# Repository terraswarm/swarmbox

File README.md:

SwarmBox
========

Testbed for the swarm of things.

Additional details documented in the [Terraswarm wiki](http://www.terraswarm.org/testbeds/wiki/Main/Hardware, "Terraswarm wiki, Hardware")

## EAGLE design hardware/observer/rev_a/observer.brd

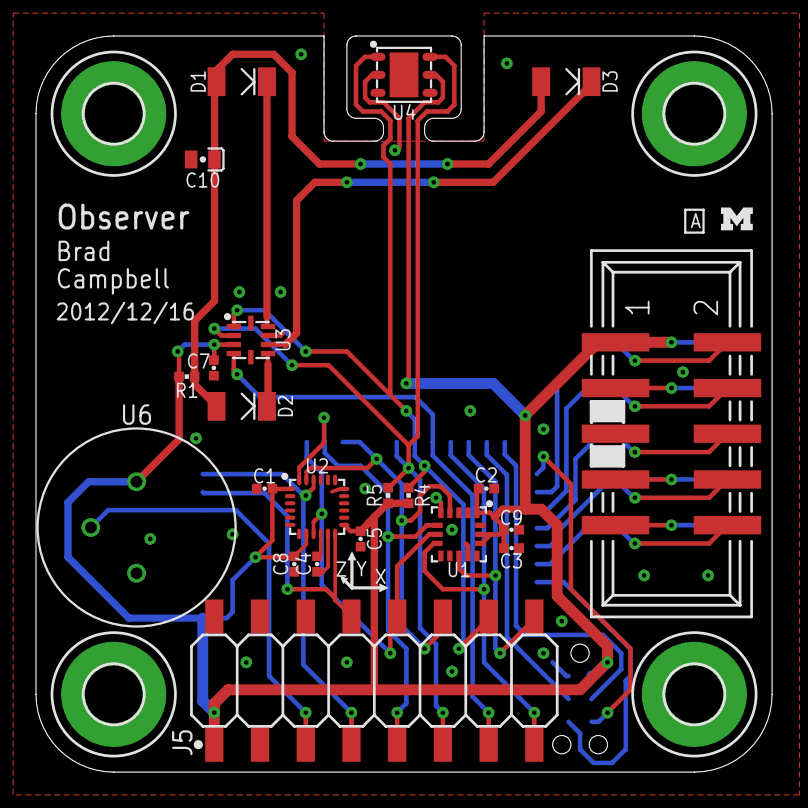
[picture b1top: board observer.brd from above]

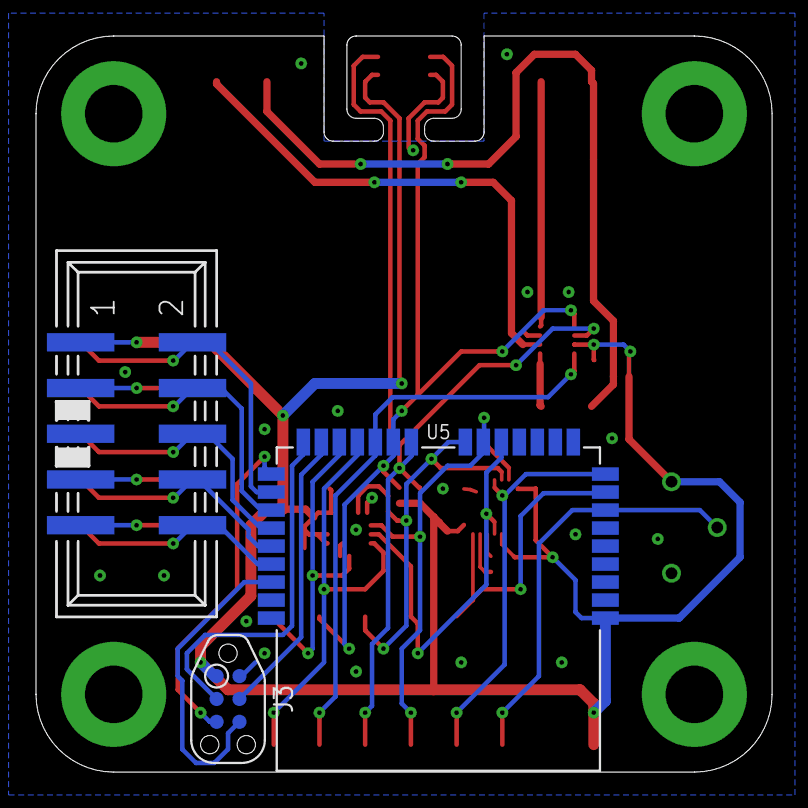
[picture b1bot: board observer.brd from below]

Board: 2 copper layers, 40.9 x 40.9 mm, 30 parts (3 on the bottom side), 29 nets.

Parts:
C1: 10nF; 0402_CAP
C2, C3, C4, C5, C7, C8: 0.1uF; 0402_CAP
C9: 10uF; 0402_CAP
C10: 22uF; CAP0603
D1, D2, D3: SFH4056
H5, H6, H7, H8: MOUNT-PAD-ROUND3.2; 3,2-PAD
J1, J2: CON_HEADER_2X05-SMD+SHROUDED; PINSHRD_SMT_2X05
J3: TC2030-CC2538-BL-NL; TC2030-IDC-NL
J5: PINHD-2X8/SMD; 2X8/SMD
LOGO1: UMICH_SOLID_TINY; UMICH_SOLID_50MIL
R1: 30; 0402_RES
R4, R5: 10k; 0402_RES
U1: LPS331AP; HCLGA-16/3MM
U2: MPU-9250; QFN-24/3MM
U3: SI1147; QFN-10/2MM
U4: SI7021; DFN-6/3MM
U5: ATUM
U6: AMN41121; AMN2

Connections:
5V: J1.3, J2.3
!ACCEL_CS: J5.7, U2.22, U5.9
!BBB_CS: J1.8, J2.8, U5.28
!PRESSURE_CS: J5.15, U1.8, U5.20
!RESET: J3.6, U5.30
ACCEL_INT: J5.8, U2.12, U5.8
BBB_GPIO: J1.7, J2.7
BBB_INT: J1.10, J2.10, U5.29
BBB_MISO: J1.4, J2.4, U5.26
BBB_MOSI: J1.2, J2.2, U5.25
BBB_SCLK: J1.6, J2.6, U5.27
BTLDR_CTRL: J3.5, U5.24
BTLDR_RX: J3.4, U5.22
BTLDR_TX: J3.3, U5.23
GND: C1.2, C2.2, C3.2, C4.2, C5.2, C7.2, C8.2, C9.2, C10.NEG, H5.B3,2, H6.B3,2, H7.B3,2, H8.B3,2, J1.9, J2.9, J3.2, J5.2, U1.5, U1.10, U1.12, U1.13, U1.16, U2.11, U2.18, U2.20, U3.8, U4.2, U5.32, U6.GND
LIGHT_INT: J5.13, U3.4, U5.19
MISO: J5.10, U1.7, U2.9, U5.14
MOSI: J5.9, U1.6, U2.24, U5.15
unnamed: C4.1, U2.10
unnamed: D1.CATHODE, U3.9
unnamed: D2.CATHODE, U3.6
unnamed: D3.CATHODE, U3.7
unnamed: C10.POS, D1.ANODE, D2.ANODE, D3.ANODE, R1.1
PIR_OUT: J5.5, U5.7, U6.OUT
PRESSURE_INT: J5.16, U1.11, U5.21
SCL: J5.11, R5.1, U3.2, U4.6, U5.17
SCLK: J5.12, U1.4, U2.23, U5.16
SDA: J5.14, R4.1, U3.1, U4.1, U5.18
VCC: C1.1, C2.1, C3.1, C5.1, C7.1, C8.1, C9.1, J1.1, J2.1, J3.1, J5.1, R1.2, R4.2, R5.2, U1.1, U1.14, U1.15, U2.1, U2.8, U2.13, U3.3, U4.5, U5.1, U6.VCC

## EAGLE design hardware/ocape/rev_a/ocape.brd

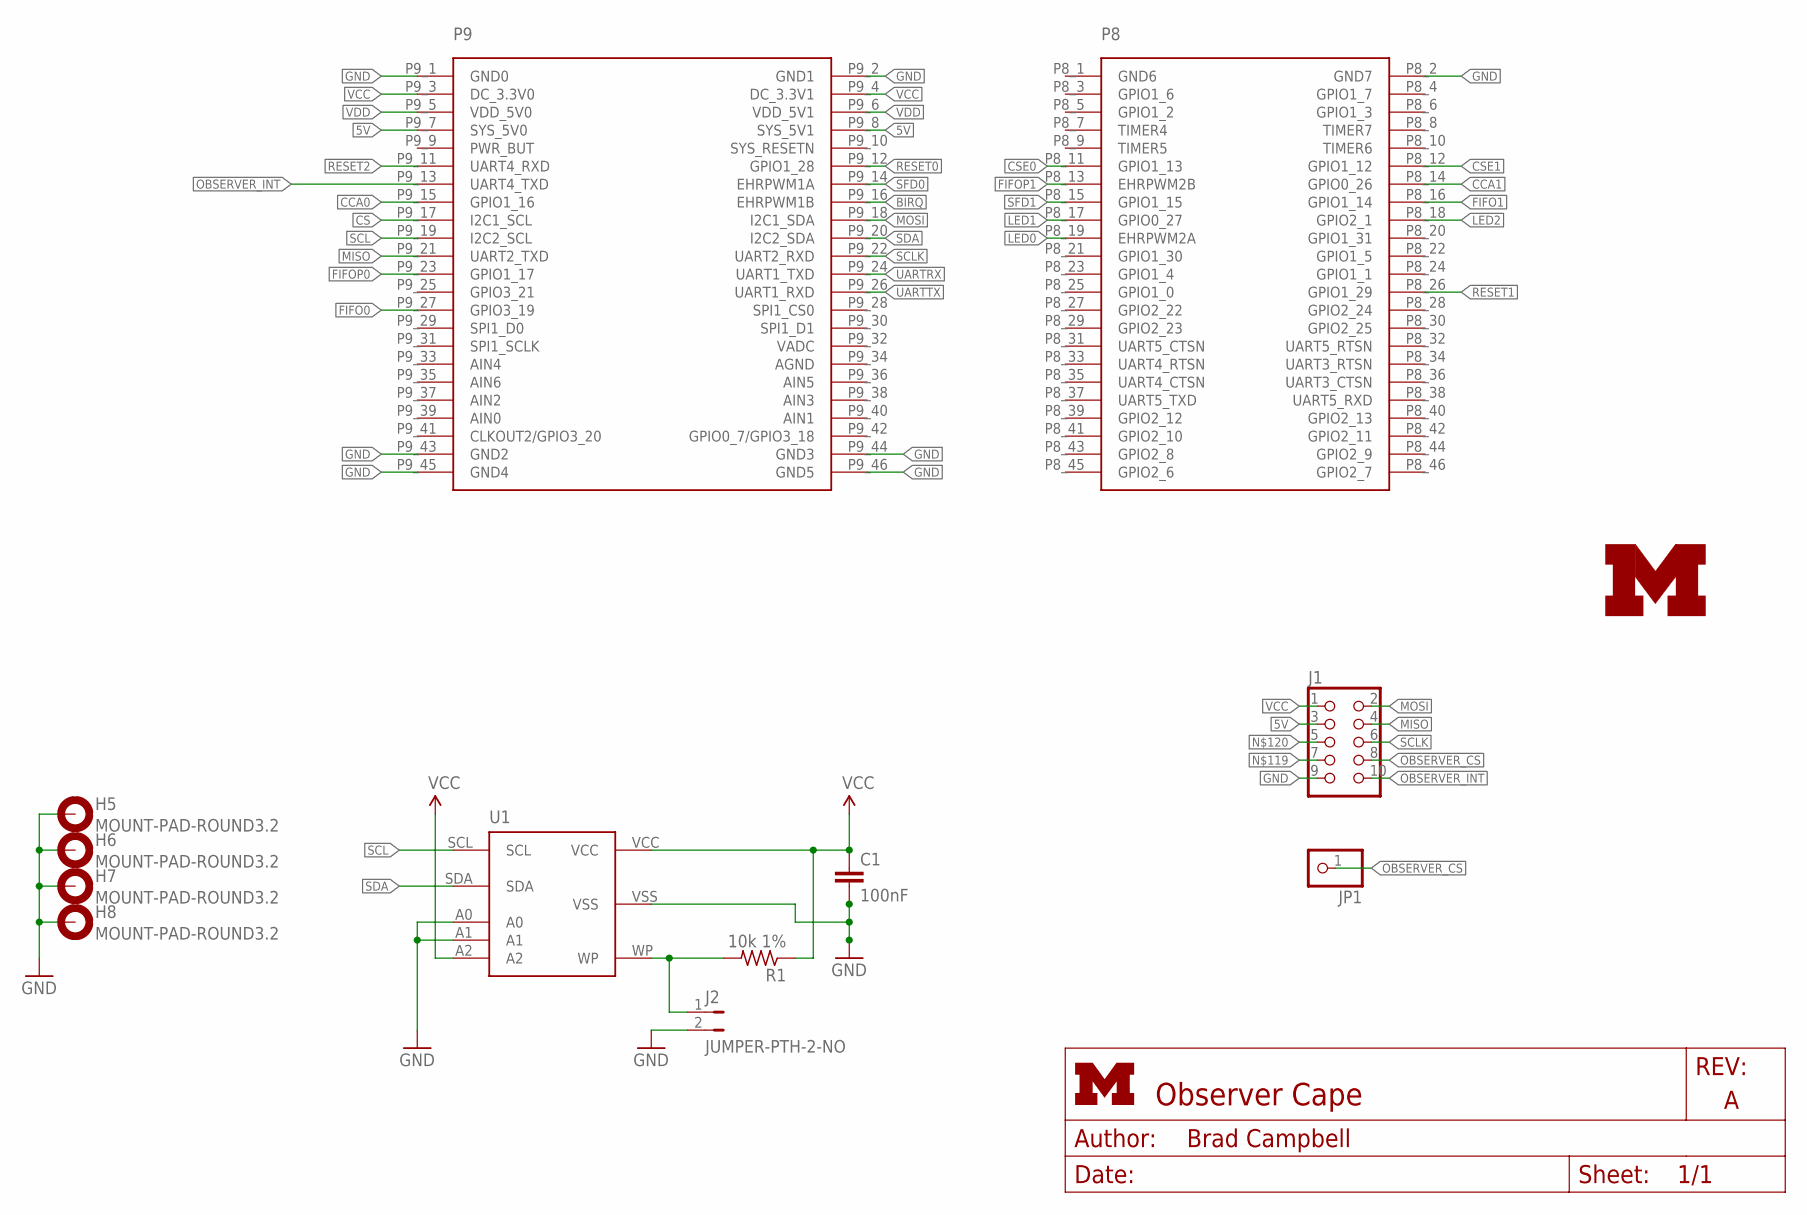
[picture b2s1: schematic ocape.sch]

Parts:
C1: 100nF; C0402; DIGIKEY 490-1318-1-ND
H5, H6, H7, H8: MOUNT-PAD-ROUND3.2; 3,2-PAD
J1: CON_HEADER_2X05-PTH+SHROUDED_A; PINSHRD_PTH_2X05
J2: JUMPER-PTH-2-NO; PTH-JUMPER-2-NO_NO_SILK
JP1: PINHD-1X1; 1X01
LOGO1: UMICH_SOLID_SMALL; UMICH_SOLID_75MIL
P9/P8: BBB_HEADERS
R1: 10k 1%; R0402; DIGIKEY RHM1.00MCDCT-ND
U1: CAT24C256WI-GT3

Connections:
5V: J1.3, P9/P8.P9_7 (SYS_5V0), P9/P8.P9_8 (SYS_5V1)
!OBSERVER_CS: J1.8, JP1.1; also elsewhere on the board
!RESET0: P9/P8.P9_12 (GPIO1_28)
!RESET1: P9/P8.P8_26 (GPIO1_29)
!RESET2: P9/P8.P9_11 (UART4_RXD)
BIRQ: P9/P8.P9_16 (EHRPWM1B)
CCA0: P9/P8.P9_15 (GPIO1_16)
CCA1: P9/P8.P8_14 (GPIO0_26)
CS: P9/P8.P9_17 (I2C1_SCL)
CSE0: P9/P8.P8_11 (GPIO1_13)
CSE1: P9/P8.P8_12 (GPIO1_12)
FIFO0: P9/P8.P9_27 (GPIO3_19)
FIFO1: P9/P8.P8_16 (GPIO1_14)
FIFOP0: P9/P8.P9_23 (GPIO1_17)
FIFOP1: P9/P8.P8_13 (EHRPWM2B)
GND: C1.2, H5.B3,2, H6.B3,2, H7.B3,2, H8.B3,2, J1.9, J2.2, P9/P8.P8_2 (GND7), P9/P8.P9_1 (GND0), P9/P8.P9_2 (GND1), P9/P8.P9_43 (GND2), P9/P8.P9_44 (GND3), P9/P8.P9_45 (GND4), P9/P8.P9_46 (GND5), U1.A0, U1.A1, U1.VSS
LED0: P9/P8.P8_19 (EHRPWM2A)
LED1: P9/P8.P8_17 (GPIO0_27)
LED2: P9/P8.P8_18 (GPIO2_1)
MISO: J1.4, P9/P8.P9_21 (UART2_TXD)
MOSI: J1.2, P9/P8.P9_18 (I2C1_SDA)
unnamed: J2.1, R1.2, U1.WP
OBSERVER_INT: J1.10, P9/P8.P9_13 (UART4_TXD)
SCL: P9/P8.P9_19 (I2C2_SCL), U1.SCL
SCLK: J1.6, P9/P8.P9_22 (UART2_RXD)
SDA: P9/P8.P9_20 (I2C2_SDA), U1.SDA
SFD0: P9/P8.P9_14 (EHRPWM1A)
SFD1: P9/P8.P8_15 (GPIO1_15)
UARTRX: P9/P8.P9_24 (UART1_TXD)
UARTTX: P9/P8.P9_26 (UART1_RXD)
VCC: C1.1, J1.1, P9/P8.P9_3 (DC_3.3V0), P9/P8.P9_4 (DC_3.3V1), R1.1, U1.A2, U1.VCC
VDD: P9/P8.P9_5 (VDD_5V0), P9/P8.P9_6 (VDD_5V1)

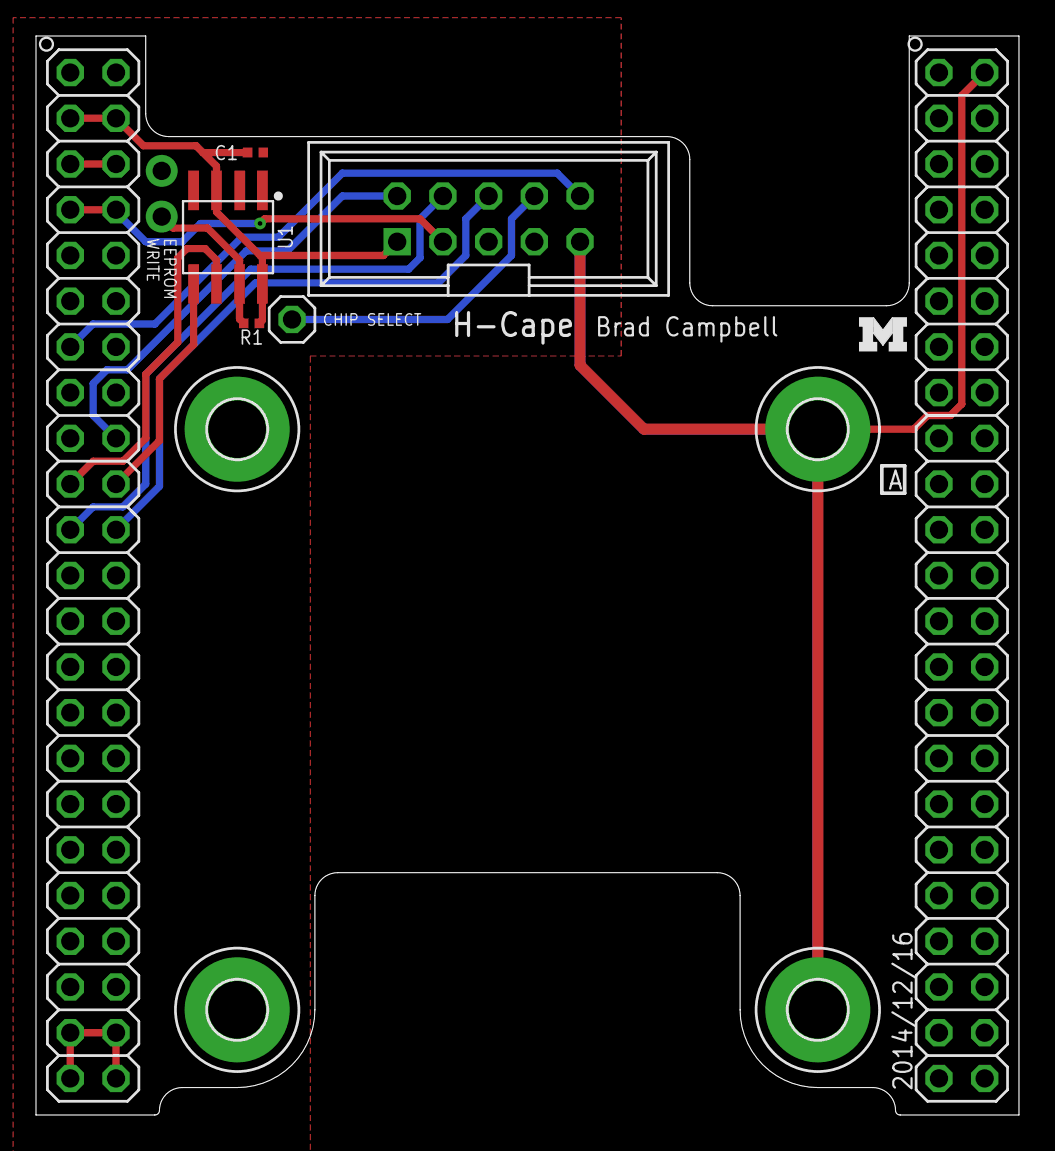
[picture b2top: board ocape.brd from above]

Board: 4 copper layers, 54.6 x 59.9 mm, 12 parts (0 on the bottom side), 12 nets.

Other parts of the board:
J3: 1X01

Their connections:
!OBSERVER_CS: J3.1; also elsewhere on the board

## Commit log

2014-12-14 started on sensor board for swarmbox
    will sense movement, temp, light, etc
2014-12-15 mostly routed
2014-12-15 pretty close on the shield board
2014-12-15 new design with mountable sensor board
    If the sensor board doesn't need to be attached elsewhere, it can be
    attached to the BBB cape.
2014-12-16 working on sensor board
2014-12-16 basically done with observer
2014-12-16 slight changes
2014-12-17 shipped rev a
2014-12-17 docs for new boards
2015-01-18 Added files and information from Swarmbox workshop
2015-01-19 distilled bom for swarmbox
2015-01-19 added swarm image
2015-01-19 added image to readme

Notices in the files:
parts and their libraries:
SparkFun-Passives: Licensing: CC v3.0 Share-Alike You are welcome to use this library for commercial purposes.
SparkFun-Aesthetics: Licensing: Creative Commons ShareAlike 4.0 International - https://creativecommons.org/licenses/by-sa/4.0
